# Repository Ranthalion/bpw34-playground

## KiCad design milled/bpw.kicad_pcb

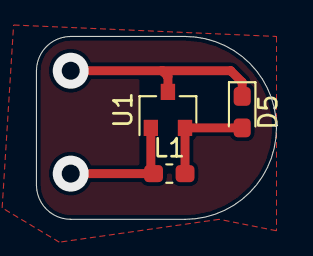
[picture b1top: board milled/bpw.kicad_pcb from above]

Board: 2 copper layers, 13.3 x 10.2 mm, 3 parts (0 on the bottom side), 3 nets.

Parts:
D5: LED; LED_0603_1608Metric_Pad1.05x0.95mm_HandSolder
L1: 100uH; L_0603_1608Metric_Pad1.05x0.95mm_HandSolder
U1: ZXSC380; SOT-23

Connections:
unnamed: L1.1, U1.1
unnamed: D5.1, U1.3
unnamed: D5.2, L1.2, U1.2

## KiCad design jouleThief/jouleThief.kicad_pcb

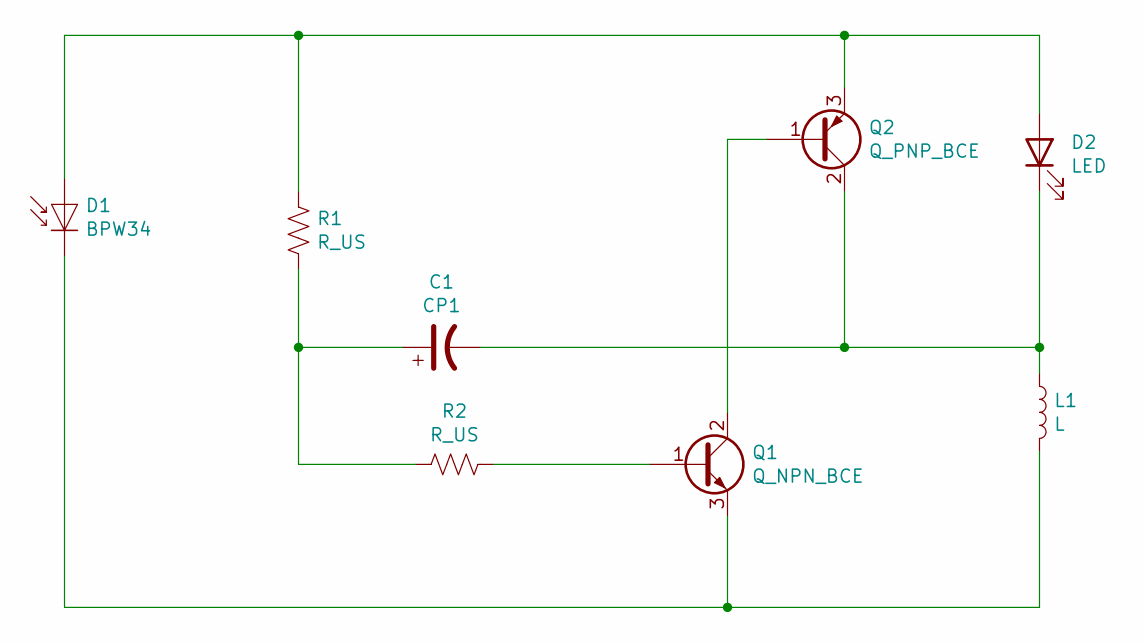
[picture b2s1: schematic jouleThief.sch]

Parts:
C1: CP1; C_1206_3216Metric_Pad1.33x1.80mm_HandSolder
D1: BPW34; Osram_DIL2_4.3x4.65mm_P5.08mm
D2: LED; LED_1206_3216Metric_Pad1.42x1.75mm_HandSolder
L1: L; L_0805_2012Metric_Pad1.15x1.40mm_HandSolder
Q1: Q_NPN_BCE; SOT-23_Handsoldering
Q2: Q_PNP_BCE; SOT-23_Handsoldering
R1, R2: R_US; R_0603_1608Metric_Pad0.98x0.95mm_HandSolder

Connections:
unnamed: C1.1, R1.2, R2.2
unnamed: C1.2, D2.1 (K), L1.1, Q2.2 (C)
unnamed: D1.1 (K), L1.2, Q1.3 (E)
unnamed: D1.2 (A), D2.2 (A), Q2.3 (E), R1.1
unnamed: Q1.1 (B), R2.1
unnamed: Q1.2 (C), Q2.1 (B)

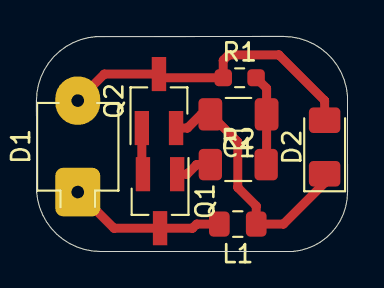
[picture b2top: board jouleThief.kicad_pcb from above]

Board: 2 copper layers, 17.3 x 11.9 mm, 8 parts (0 on the bottom side), 6 nets.

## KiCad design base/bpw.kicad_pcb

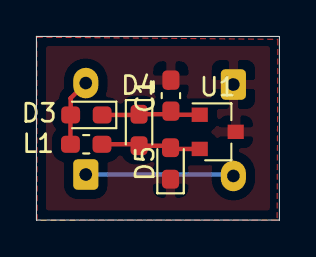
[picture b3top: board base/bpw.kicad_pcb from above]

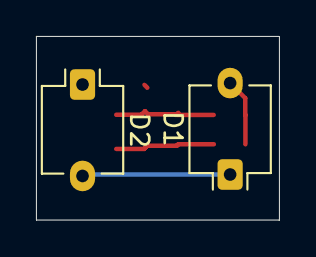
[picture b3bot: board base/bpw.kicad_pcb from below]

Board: 2 copper layers, 13.5 x 10.2 mm, 8 parts (2 on the bottom side), 5 nets.

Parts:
C1: 1uF; C_0603_1608Metric_Pad1.08x0.95mm_HandSolder
D1, D2: BPW34; Osram_DIL2_4.3x4.65mm_P5.08mm
D3, D4: D_Schottky; D_0603_1608Metric_Pad1.05x0.95mm_HandSolder
D5: LED; LED_0603_1608Metric_Pad1.05x0.95mm_HandSolder
L1: 100uH; L_0603_1608Metric_Pad1.05x0.95mm_HandSolder
U1: ZXSC380; SOT-23

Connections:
GND: C1.2, D2.1, D5.1, U1.3
unnamed: C1.1, D3.1, D4.1, U1.1
unnamed: D1.1, D2.2
unnamed: D1.2, D3.2, L1.1
unnamed: D4.2, D5.2, L1.2, U1.2

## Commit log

2021-01-08 milled pcb
2021-01-10 Joule Thief
